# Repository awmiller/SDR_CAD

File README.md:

# sdr_eagle
various designs for different stages of development and manufacturers.

## 1: Clone into the "eagle" directory created by the Eagle CAD installer
## 2: Copy contents of "copy_to_lbr" into your "<Eagle Install dir>/lbr"

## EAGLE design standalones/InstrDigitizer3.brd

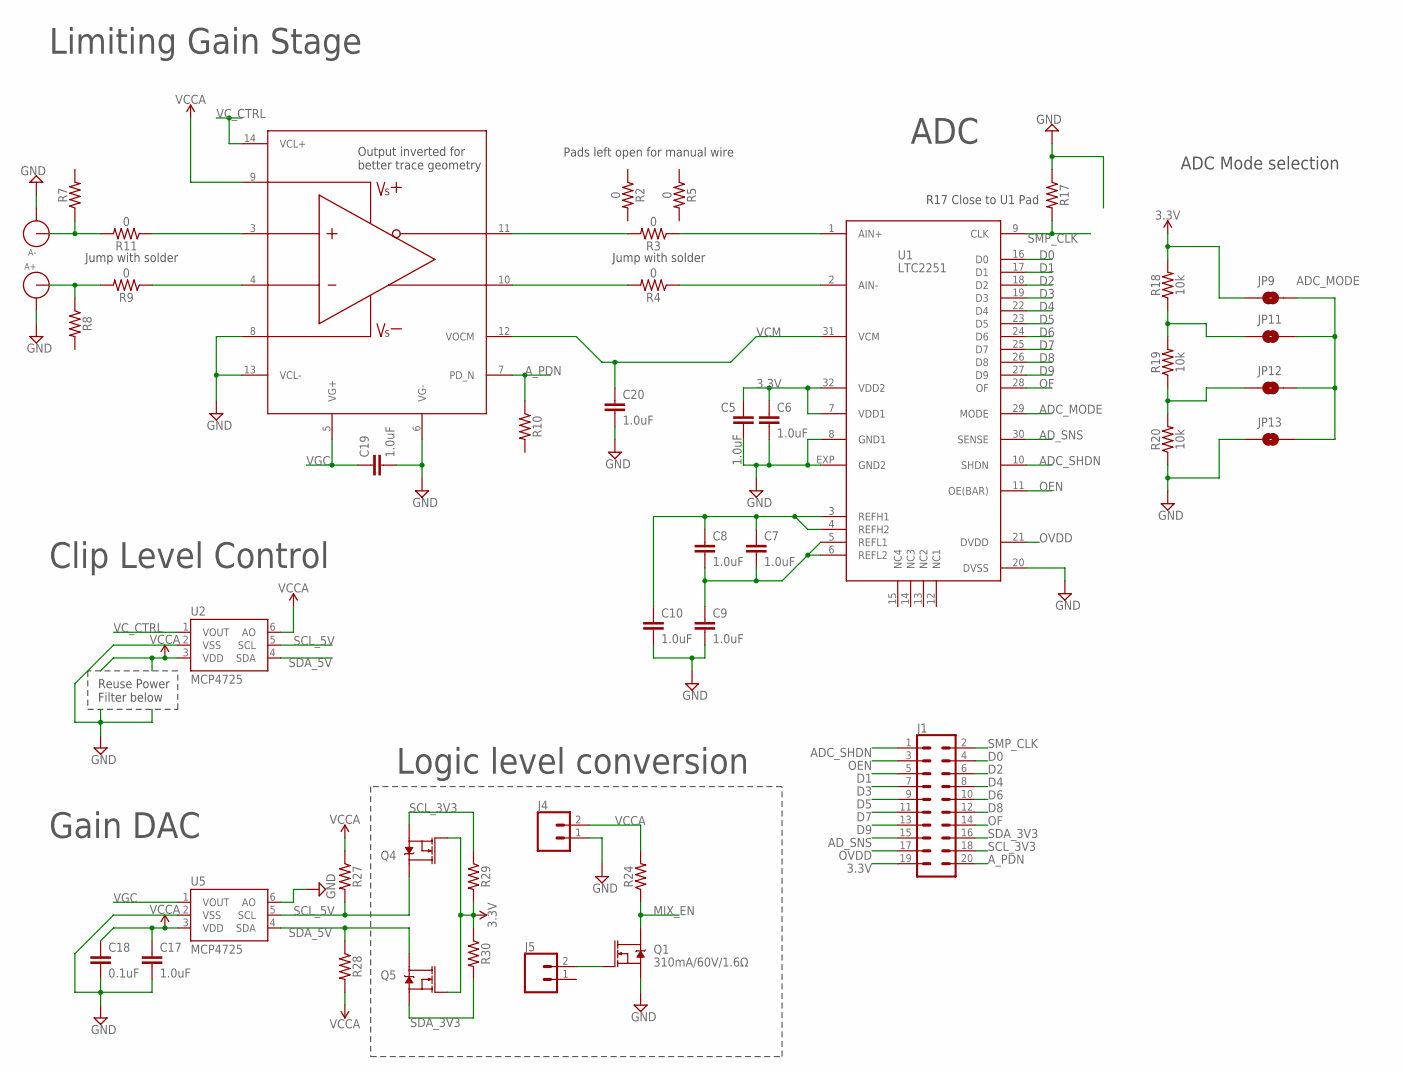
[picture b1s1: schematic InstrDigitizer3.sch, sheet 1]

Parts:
A+: LINX-SMA-EDGE-0.062; CONSMA003.062
A-: LINX-SMA-EDGE-0.062; CONSMA003.062
C5, C6, C7, C8, C9, C10, C17, C19, C20: 1.0uF; 0402
C18: 0.1uF; 0402
J1: CONN_10X2; 2X10
J4, J5: CONN_02; 1X02
JP9, JP11, JP12, JP13: JUMPER-SMT_2_NO_NO-SILK; SMT-JUMPER_2_NO_NO-SILK
Q1: 310mA/60V/1.6Ω; SOT323
Q4, Q5: MOSFET-NCH-AO3404A; SOT23-3
R2, R3, R4, R5, R9, R11: 0; 0402
R7, R8, R10, R17, R24, R27, R28, R29, R30: 0402
R18, R19, R20: 10k; 0402
U1: LTC2251; HVQFN32
U2, U5: MCP4725; SOT23-6
U$1: THS7530; TSSOP14

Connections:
3.3V: C5.1, C6.1, J1.19, JP9.1, Q4.1 (G), Q5.1 (G), R18.2, R29.2, R30.1, U1.7 (VDD1), U1.32 (VDD2); also elsewhere on the board
ADC_MODE: JP9.2, JP11.2, JP12.2, JP13.2, U1.29 (MODE)
ADC_SHDN: J1.1, U1.10 (SHDN)
AD_SNS: J1.15, U1.30 (SENSE)
A_PDN: J1.20, R10.1, U$1.7 (PD_N)
D0: J1.4, U1.16 (D0)
D1: J1.5, U1.17 (D1)
D2: J1.6, U1.18 (D2)
D3: J1.7, U1.19 (D3)
D4: J1.8, U1.22 (D4)
D5: J1.9, U1.23 (D5)
D6: J1.10, U1.24 (D6)
D7: J1.11, U1.25 (D7)
D8: J1.12, U1.26 (D8)
D9: J1.13, U1.27 (D9)
GND: A+.GND1, A+.GND2, A+.GND3, A+.GND4, A-.GND1, A-.GND2, A-.GND3, A-.GND4, C5.2, C6.2, C9.2, C10.2, C17.2, C18.2, C19.2, C20.2, J4.1, JP13.1, Q1.2 (S), R17.1, R20.1, U1.8 (GND1), U1.20 (DVSS), U1.EXP (GND2), U2.2 (VSS), U5.2 (VSS), U5.6 (AO), U$1.6 (VG-), U$1.8, U$1.13 (VCL-); also elsewhere on the board
MIX_EN: Q1.3 (D), R24.1; also elsewhere on the board
unnamed: R11.1, U$1.3
unnamed: A+.ANT, R8.1, R9.2
unnamed: J5.2, Q1.1 (G)
unnamed: R3.1, U1.1 (AIN+)
unnamed: R3.2, U$1.11 (VO-)
unnamed: R4.1, U1.2 (AIN-)
unnamed: R4.2, U$1.10 (VO+)
unnamed: A-.ANT, R7.1, R11.2
unnamed: R9.1, U$1.4
unnamed: C7.1, C8.1, C10.1, U1.3 (REFH1), U1.4 (REFH2)
unnamed: JP12.1, R19.1, R20.2
unnamed: C7.2, C8.2, C9.1, U1.5 (REFL1), U1.6 (REFL2)
unnamed: JP11.1, R18.1, R19.2
OEN: J1.3, U1.11 (OE(BAR))
OF: J1.14, U1.28 (OF)
OVDD: J1.17, U1.21 (DVDD)
SCL_3V3: J1.18, Q4.2 (S), R29.1
SCL_5V: Q4.3 (D), R27.2, U2.5 (SCL), U5.5 (SCL)
SDA_3V3: J1.16, Q5.2 (S), R30.2
SDA_5V: Q5.3 (D), R28.1, U2.4 (SDA), U5.4 (SDA)
SMP_CLK: J1.2, R17.2, U1.9 (CLK)
VCCA: C17.1, C18.1, J4.2, R24.2, R27.1, R28.2, U2.3 (VDD), U2.6 (AO), U5.3 (VDD), U$1.9; also elsewhere on the board
VCM: C20.1, U1.31 (VCM), U$1.12 (VOCM)
VC_CTRL: U2.1 (VOUT), U$1.14 (VCL+)
VGC: C19.1, U5.1 (VOUT), U$1.5 (VG+)

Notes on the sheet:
R17 Close to U1 Pad
Logic level conversion
Limiting Gain Stage
ADC
Gain DAC
ADC Mode selection
Jump with solder
Pads left open for manual wire
Clip Level Control
Output inverted for better trace geometry
Reuse Power Filter below

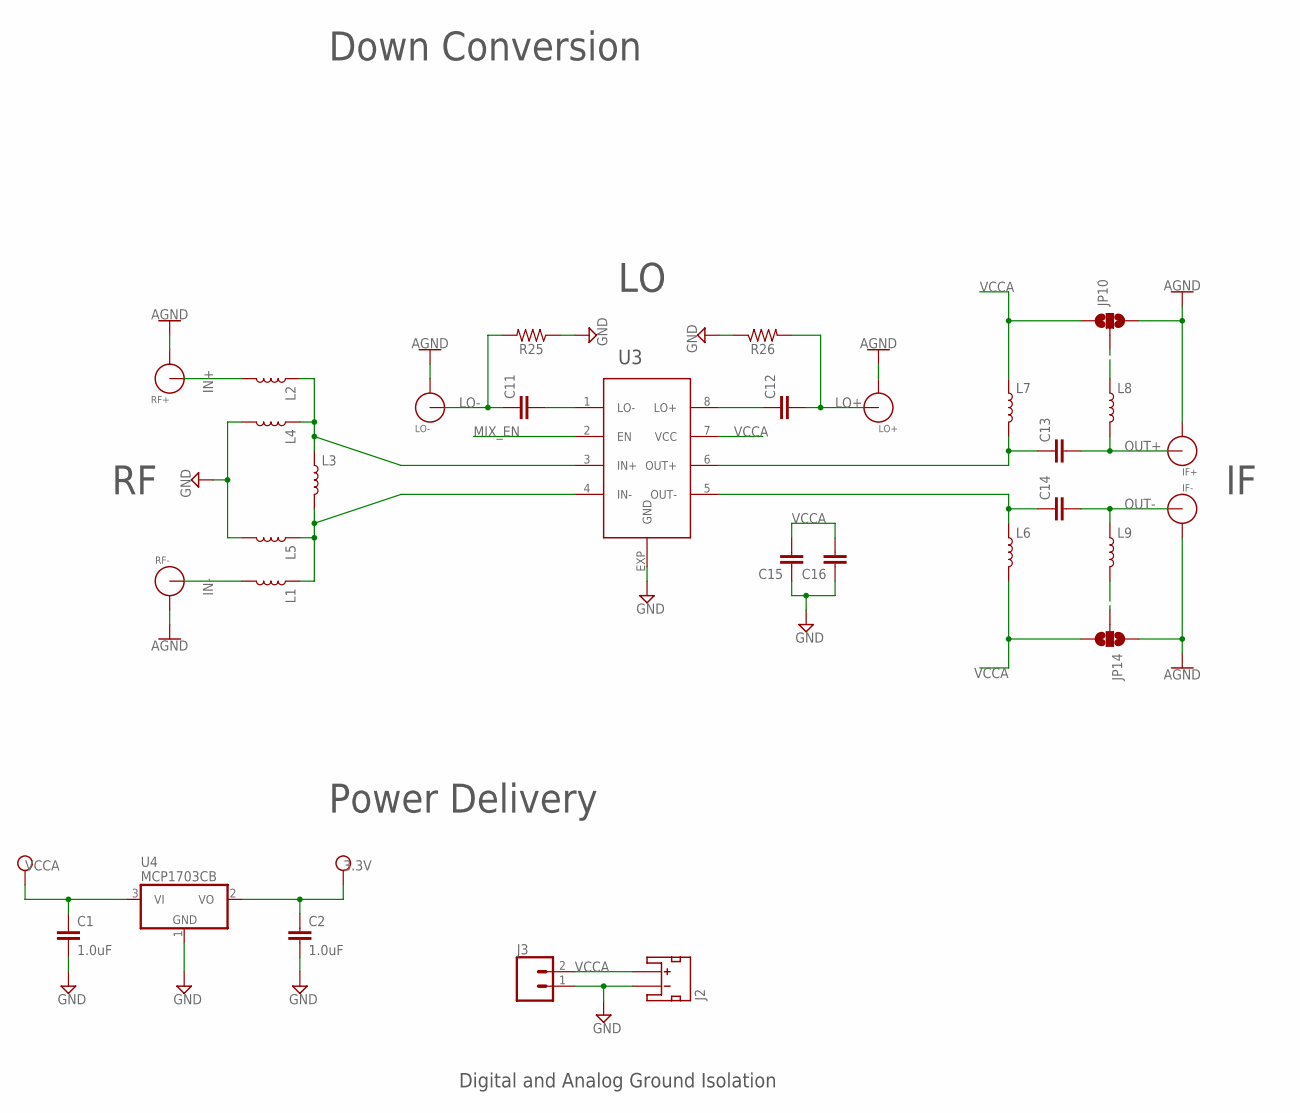
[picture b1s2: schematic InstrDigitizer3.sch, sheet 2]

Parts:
C1, C2: 1.0uF; 0402
C11, C12, C13, C14, C15, C16: 1.0UF-0402-16V-10%; 0402
IF+: LINX-SMA-EDGE-0.062; CONSMA003.062
IF-: LINX-SMA-EDGE-0.062; CONSMA003.062
J2: JST_2MM_MALE; JST-2-SMD
J3: CONN_02; 1X02
JP10, JP14: JUMPER-SMT_3_NO_NO-SILK; SMT-JUMPER_3_NO_NO-SILK
L1, L2, L3, L4, L5, L6, L7, L8, L9: INDUCTOR-0603-33NH; 0603
LO+: LINX-SMA-EDGE-0.062; CONSMA003.062
LO-: LINX-SMA-EDGE-0.062; CONSMA003.062
R25, R26: 0402
RF+: LINX-SMA-EDGE-0.062; CONSMA003.062
RF-: LINX-SMA-EDGE-0.062; CONSMA003.062
U3: LT5560; DFN8-3X3
U4: MCP1703CB; SOT23

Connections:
3.3V: C2.1, U4.2 (VO); also elsewhere on the board
GND: C1.2, C2.2, C15.1, C16.1, IF+.GND1, IF+.GND2, IF+.GND3, IF+.GND4, IF-.GND1, IF-.GND2, IF-.GND3, IF-.GND4, J2.1 (-), J3.1, JP10.3, JP14.1, L4.2, L5.2, LO+.GND1, LO+.GND2, LO+.GND3, LO+.GND4, LO-.GND1, LO-.GND2, LO-.GND3, LO-.GND4, R25.1, R26.1, RF+.GND1, RF+.GND2, RF+.GND3, RF+.GND4, RF-.GND1, RF-.GND2, RF-.GND3, RF-.GND4, U3.EXP (GND), U4.1 (GND); also elsewhere on the board
IN+: L2.2, RF+.ANT
IN-: L1.2, RF-.ANT
LO+: C12.2, LO+.ANT, R26.2
LO-: C11.1, LO-.ANT, R25.2
MIX_EN: U3.2 (EN); also elsewhere on the board
N98: L1.1, L3.2, L5.1, U3.4 (IN-)
unnamed: C11.2, U3.1 (LO-)
unnamed: C12.1, U3.8 (LO+)
unnamed: L2.1, L3.1, L4.1, U3.3 (IN+)
unnamed: C14.1, L6.1, U3.5 (OUT-)
unnamed: C13.1, L7.2, U3.6 (OUT+)
unnamed: JP10.2, L8.1
unnamed: JP14.2, L9.2
OUT+: C13.2, IF+.ANT, L8.2
OUT-: C14.2, IF-.ANT, L9.1
VCCA: C1.1, C15.2, C16.2, J2.2 (+), J3.2, JP10.1, JP14.3, L6.2, L7.1, U3.7 (VCC), U4.3 (VI); also elsewhere on the board

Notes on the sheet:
Digital and Analog Ground Isolation
Power Delivery
Down Conversion

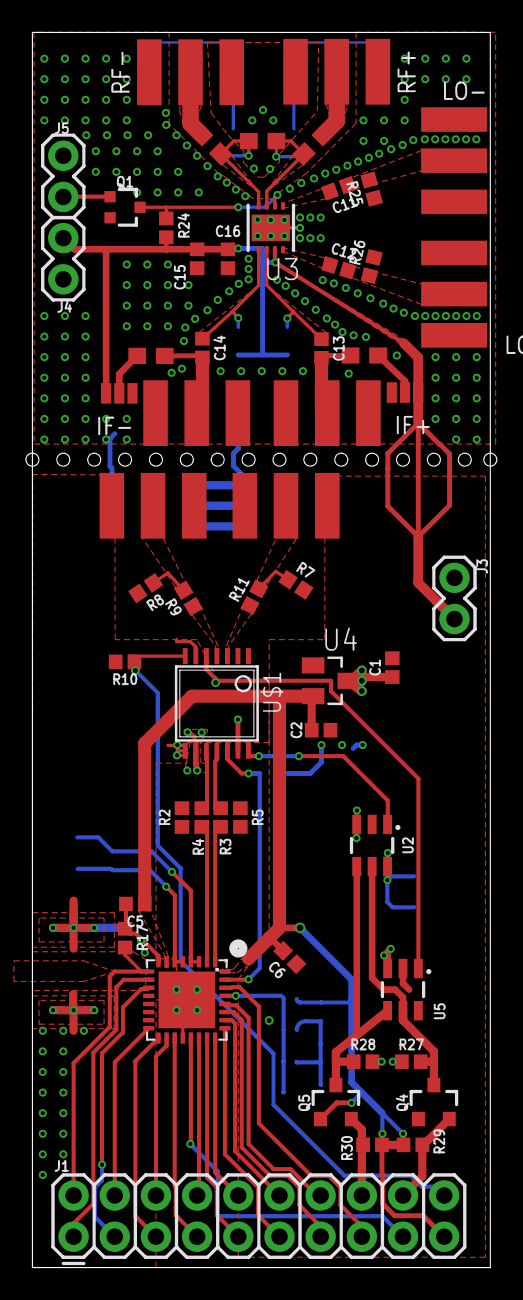
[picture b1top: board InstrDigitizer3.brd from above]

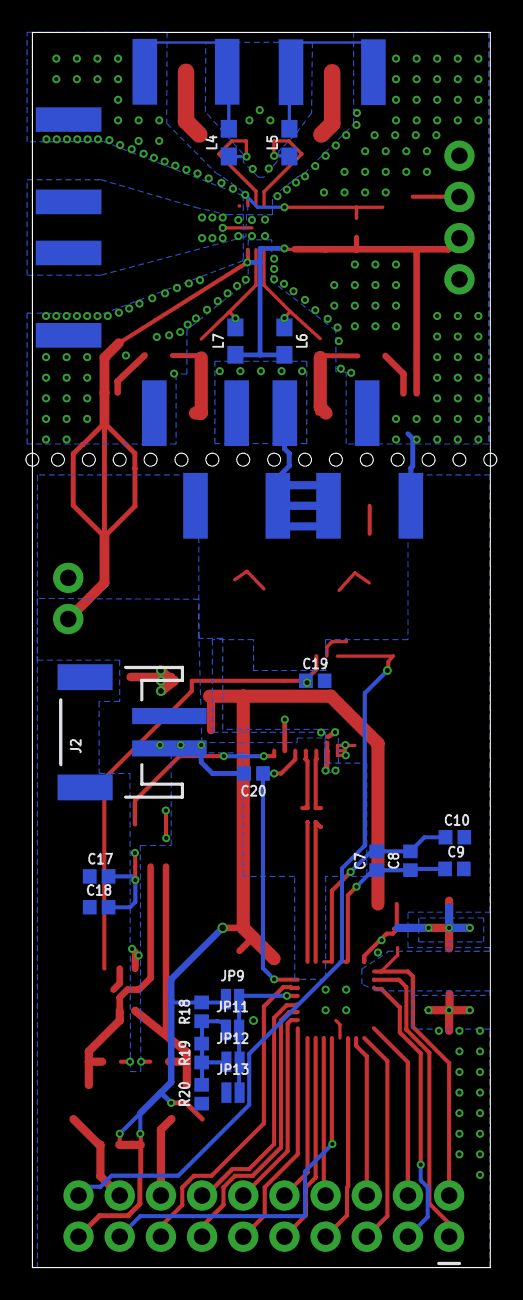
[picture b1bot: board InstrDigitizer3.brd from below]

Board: 2 copper layers, 28.2 x 76.2 mm, 75 parts (20 on the bottom side), 56 nets.

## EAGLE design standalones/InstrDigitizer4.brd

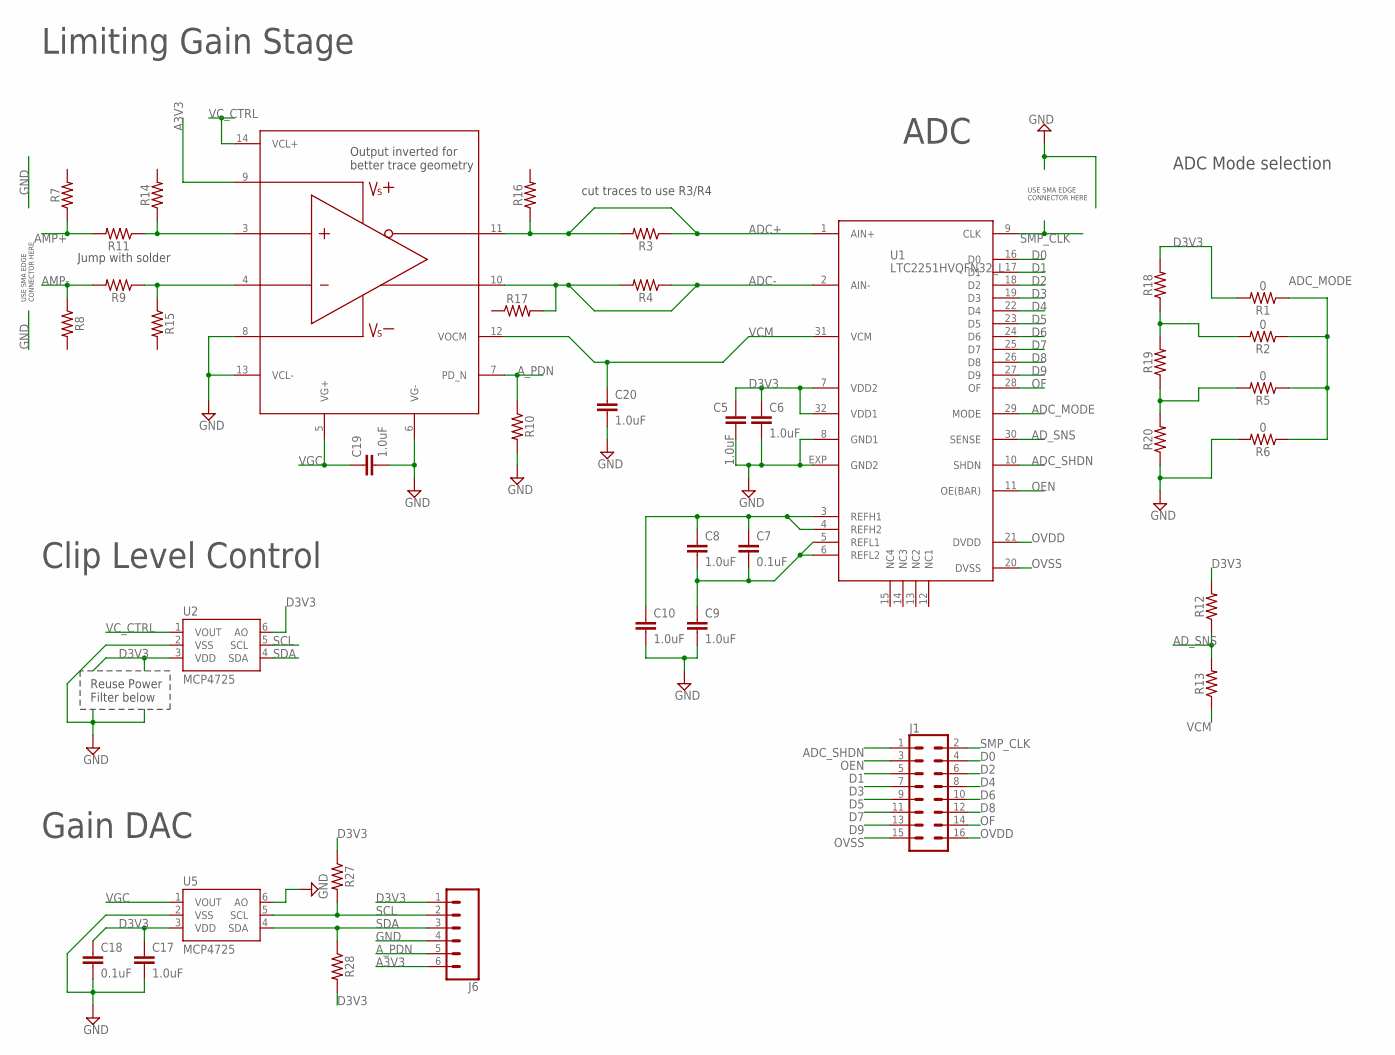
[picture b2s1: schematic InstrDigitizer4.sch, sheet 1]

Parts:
C5, C6, C8, C9, C10, C17, C19, C20: 1.0uF; 0402
C7, C18: 0.1uF; 0402
J1: CONN_08X2; 2X8
J6: CONN_06SILK_FEMALE_PTH; 1X06
R1, R2, R5, R6: 0; 0402
R3, R4, R7, R8, R9, R10, R11, R12, R13, R14, R15, R16, R17, R18, R19, R20, R27, R28: 0402
U1: LTC2251HVQFN32_L; HVQFN32_LONG
U2, U5: MCP4725; SOT23-6
U$1: THS7530TSSOP14_LONG; TSSOP14_LONG

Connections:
A3V3: J6.6, U$1.9; also elsewhere on the board
ADC+: R3.1, R3.2, R16.1, U1.1 (AIN+), U$1.11 (VO-)
ADC-: R4.1, R4.2, R17.2, U1.2 (AIN-), U$1.10 (VO+)
ADC_MODE: R1.1, R2.1, R5.1, R6.1, U1.29 (MODE)
ADC_SHDN: J1.1, U1.10 (SHDN)
AD_SNS: R12.1, R13.2, U1.30 (SENSE)
AMP+: R7.1, R11.2
AMP-: R8.1, R9.2
A_PDN: J6.5, R10.1, U$1.7 (PD_N)
D0: J1.4, U1.16 (D0)
D1: J1.5, U1.17 (D1)
D2: J1.6, U1.18 (D2)
D3: J1.7, U1.19 (D3)
D3V3: C5.1, C6.1, C17.1, C18.1, J6.1, R1.2, R12.2, R18.2, R27.1, R28.2, U1.7 (VDD2), U1.32 (VDD1), U2.3 (VDD), U2.6 (AO), U5.3 (VDD); also elsewhere on the board
D4: J1.8, U1.22 (D4)
D5: J1.9, U1.23 (D5)
D6: J1.10, U1.24 (D6)
D7: J1.11, U1.25 (D7)
D8: J1.12, U1.26 (D8)
D9: J1.13, U1.27 (D9)
GND: C5.2, C6.2, C9.2, C10.2, C17.2, C18.2, C19.2, C20.2, J6.4, R6.2, R10.2, R20.1, U1.8 (GND1), U1.EXP (GND2), U2.2 (VSS), U5.2 (VSS), U5.6 (AO), U$1.6 (VG-), U$1.8, U$1.13 (VCL-); also elsewhere on the board
unnamed: R11.1, R14.1, U$1.3
unnamed: R9.1, R15.1, U$1.4
unnamed: C7.1, C8.1, C10.1, U1.3 (REFH1), U1.4 (REFH2)
unnamed: R5.2, R19.1, R20.2
unnamed: C7.2, C8.2, C9.1, U1.5 (REFL1), U1.6 (REFL2)
unnamed: R2.2, R18.1, R19.2
OEN: J1.3, U1.11 (OE(BAR))
OF: J1.14, U1.28 (OF)
OVDD: J1.16, U1.21 (DVDD)
OVSS: J1.15, U1.20 (DVSS)
SCL: J6.2, R27.2, U2.5 (SCL), U5.5 (SCL)
SDA: J6.3, R28.1, U2.4 (SDA), U5.4 (SDA)
SMP_CLK: J1.2, U1.9 (CLK)
VCM: C20.1, R13.1, U1.31 (VCM), U$1.12 (VOCM)
VC_CTRL: U2.1 (VOUT), U$1.14 (VCL+)
VGC: C19.1, U5.1 (VOUT), U$1.5 (VG+)

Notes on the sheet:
Limiting Gain Stage
ADC
Gain DAC
ADC Mode selection
Clip Level Control
Output inverted for better trace geometry
Reuse Power Filter below
Jump with solder
USE SMA EDGE CONNECTOR HERE
cut traces to use R3/R4

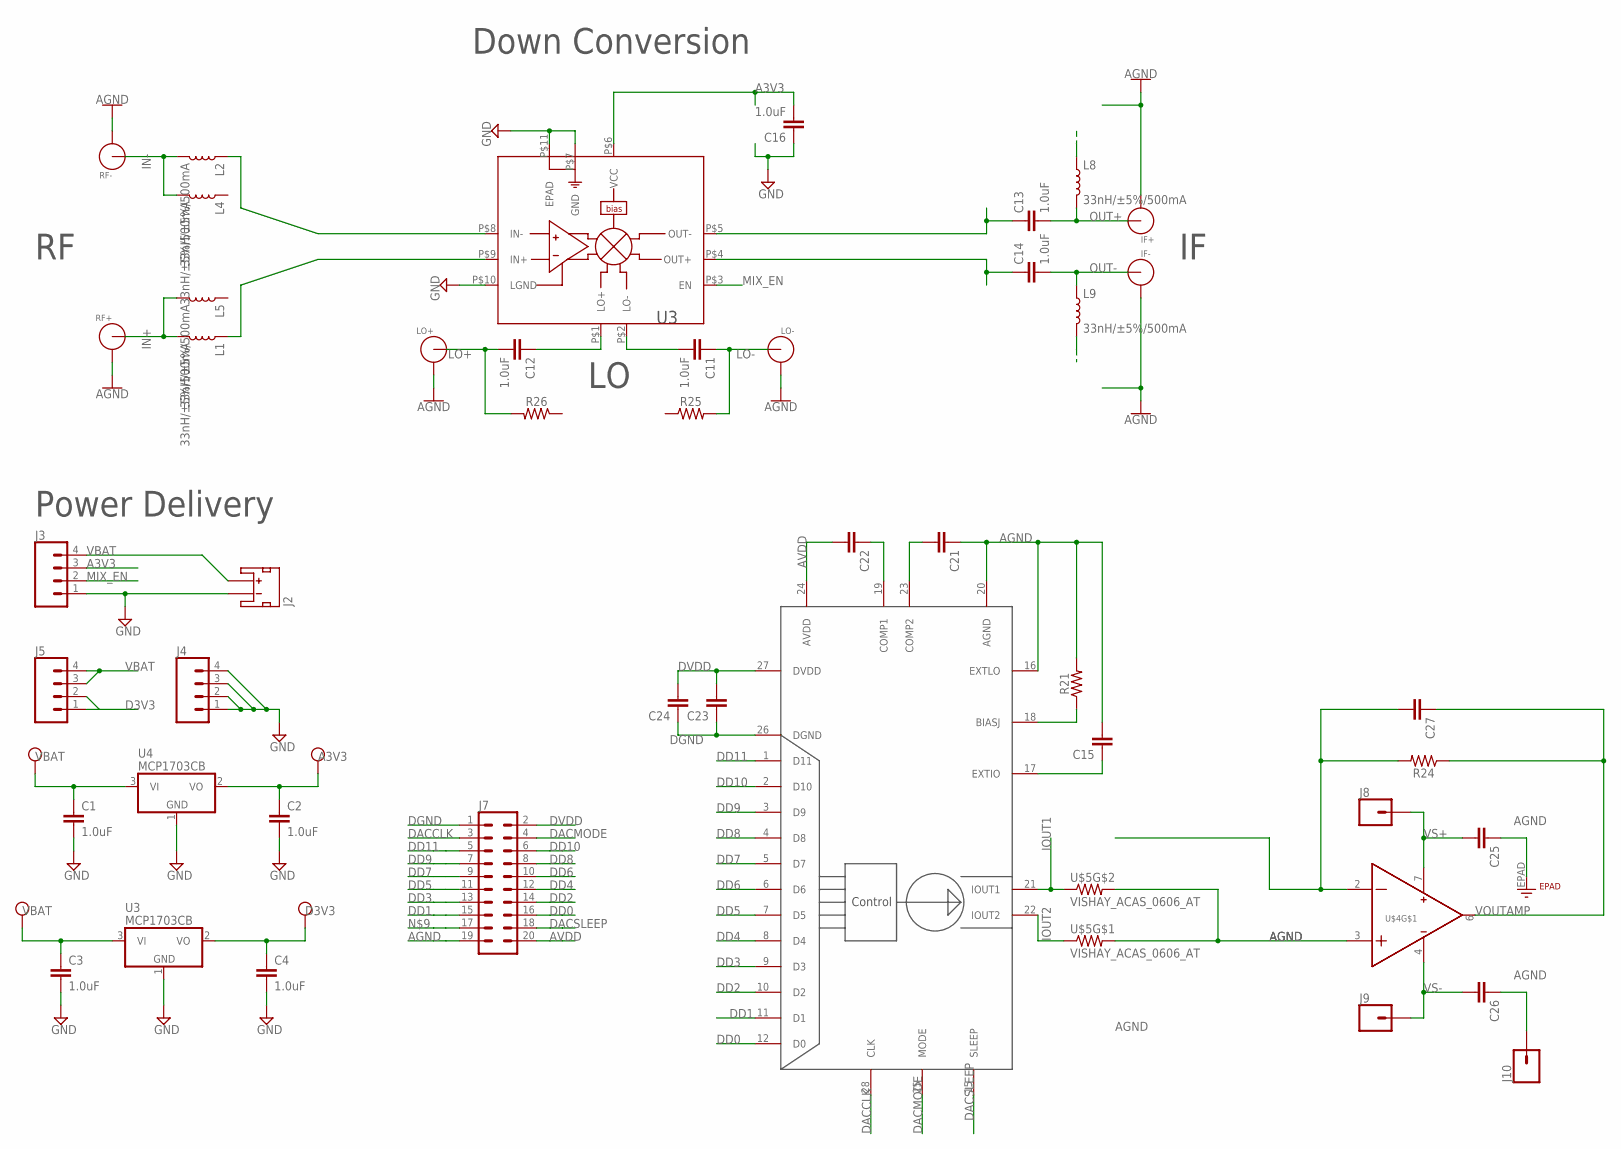
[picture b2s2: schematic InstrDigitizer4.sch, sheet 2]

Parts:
C1, C2, C3, C4, C11, C12, C13, C14, C16: 1.0uF; 0402
C15, C21, C22, C23, C24, C25, C26, C27: 1.0UF-0402-16V-10%; 0402
IF+: LINX-SMA-EDGE-0.062; CONSMA003.062
IF-: LINX-SMA-EDGE-0.062; CONSMA003.062
J2: JST_2MM_MALE; JST-2-SMD
J3, J4, J5: CONN_04; 1X04
J7: CONN_10X2; 2X10
J8, J9, J10: CONN_01; 1X01
L1, L2, L4, L5, L8, L9: 33nH/±5%/500mA; 0603
LO+: LINX-SMA-EDGE-0.062; CONSMA003.062
LO-: LINX-SMA-EDGE-0.062; CONSMA003.062
R21, R24, R25, R26: 0402
RF+: LINX-SMA-EDGE-0.062; CONSMA003.062
RF-: LINX-SMA-EDGE-0.062; CONSMA003.062
U3, U4: MCP1703CB; SOT23
U$2: THS5661ASOIC28; SOIC-28
U$3: LTC5562LONG; QFN_10_2X2MM_05-08-1534_LONG
U$4: THS4011SOIC8-EPAD; SO-08
U$5: VISHAY_ACAS_0606_AT; VISHAY_ACAS0606AT

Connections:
A3V3: C2.1, C16.2, J3.3, U4.2 (VO), U$3.P$6 (VCC); also elsewhere on the board
AGND: C15.2, C21.1, C25.1, C26.1, J7.19, J10.1, R21.2, U$2.16 (EXTLO), U$2.20 (AGND), U$4.3 (IN+), U$4.EPAD, U$5.P$3 (2), U$5.P$4 (2)
AVDD: C22.2, J7.20, U$2.24 (AVDD)
D3V3: C4.1, J5.1, J5.2, U3.2 (VO); also elsewhere on the board
DACCLK: J7.3, U$2.28 (CLK)
DACMODE: J7.4, U$2.25 (MODE)
DACSLEEP: J7.18, U$2.15 (SLEEP)
DD0: J7.16, U$2.12 (D0)
DD1: J7.15, U$2.11 (D1)
DD2: J7.14, U$2.10 (D2)
DD3: J7.13, U$2.9 (D3)
DD4: J7.12, U$2.8 (D4)
DD5: J7.11, U$2.7 (D5)
DD6: J7.10, U$2.6 (D6)
DD7: J7.9, U$2.5 (D7)
DD8: J7.8, U$2.4 (D8)
DD9: J7.7, U$2.3 (D9)
DD10: J7.6, U$2.2 (D10)
DD11: J7.5, U$2.1 (D11)
DGND: C23.1, C24.1, J7.1, U$2.26 (DGND)
DVDD: C23.2, C24.2, J7.2, U$2.27 (DVDD)
GND: C1.2, C2.2, C3.2, C4.2, C16.1, IF+.GND1, IF+.GND2, IF+.GND3, IF+.GND4, IF-.GND1, IF-.GND2, IF-.GND3, IF-.GND4, J2.1 (-), J3.1, J4.1, J4.2, J4.3, J4.4, LO+.GND1, LO+.GND2, LO+.GND3, LO+.GND4, LO-.GND1, LO-.GND2, LO-.GND3, LO-.GND4, RF+.GND1, RF+.GND2, RF+.GND3, RF+.GND4, RF-.GND1, RF-.GND2, RF-.GND3, RF-.GND4, U3.1 (GND), U4.1 (GND), U$3.P$7 (GND), U$3.P$10 (LGND), U$3.P$11 (EPAD); also elsewhere on the board
IN+: L1.2, L5.2, RF+.ANT
IN-: L2.2, L4.2, RF-.ANT
IOUT1: U$2.21 (IOUT1), U$5.P$2 (1)
IOUT2: U$2.22 (IOUT2), U$5.P$1 (1)
LO+: C12.2, LO+.ANT, R26.2
LO-: C11.1, LO-.ANT, R25.2
MIX_EN: J3.2, U$3.P$3 (EN)
N98: L1.1, U$3.P$9 (IN+)
unnamed: C15.1, U$2.17 (EXTIO)
unnamed: R21.1, U$2.18 (BIASJ)
unnamed: C21.2, U$2.23 (COMP2)
unnamed: C22.1, U$2.19 (COMP1)
unnamed: C27.2, R24.2, U$4.2 (IN-)
unnamed: C11.2, U$3.P$2 (LO-)
unnamed: C12.1, U$3.P$1 (LO+)
unnamed: L2.1, U$3.P$8 (IN-)
unnamed: C14.1, U$3.P$4 (OUT+)
unnamed: C13.1, U$3.P$5 (OUT-)
OUT+: C13.2, IF+.ANT, L8.2
OUT-: C14.2, IF-.ANT, L9.1
VBAT: C1.1, C3.1, J2.2 (+), J3.4, J5.3, J5.4, U3.3 (VI), U4.3 (VI)
VOUTAMP: C27.1, R24.1, U$4.6 (OUT)
VS+: C25.2, J8.1, U$4.7 (VCC+)
VS-: C26.2, J9.1, U$4.4 (VCC-)

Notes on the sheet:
Power Delivery
Down Conversion

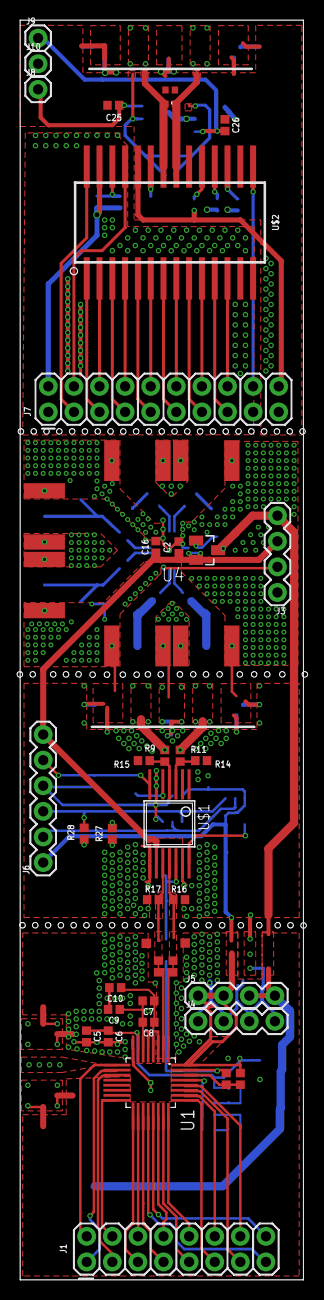
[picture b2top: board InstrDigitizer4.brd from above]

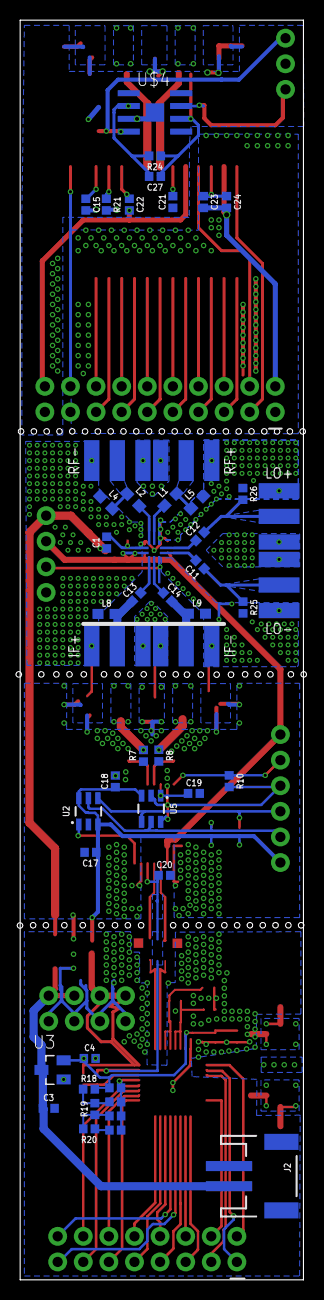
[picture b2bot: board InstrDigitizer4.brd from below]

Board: 2 copper layers, 28.1 x 125.0 mm, 85 parts (49 on the bottom side), 80 nets.

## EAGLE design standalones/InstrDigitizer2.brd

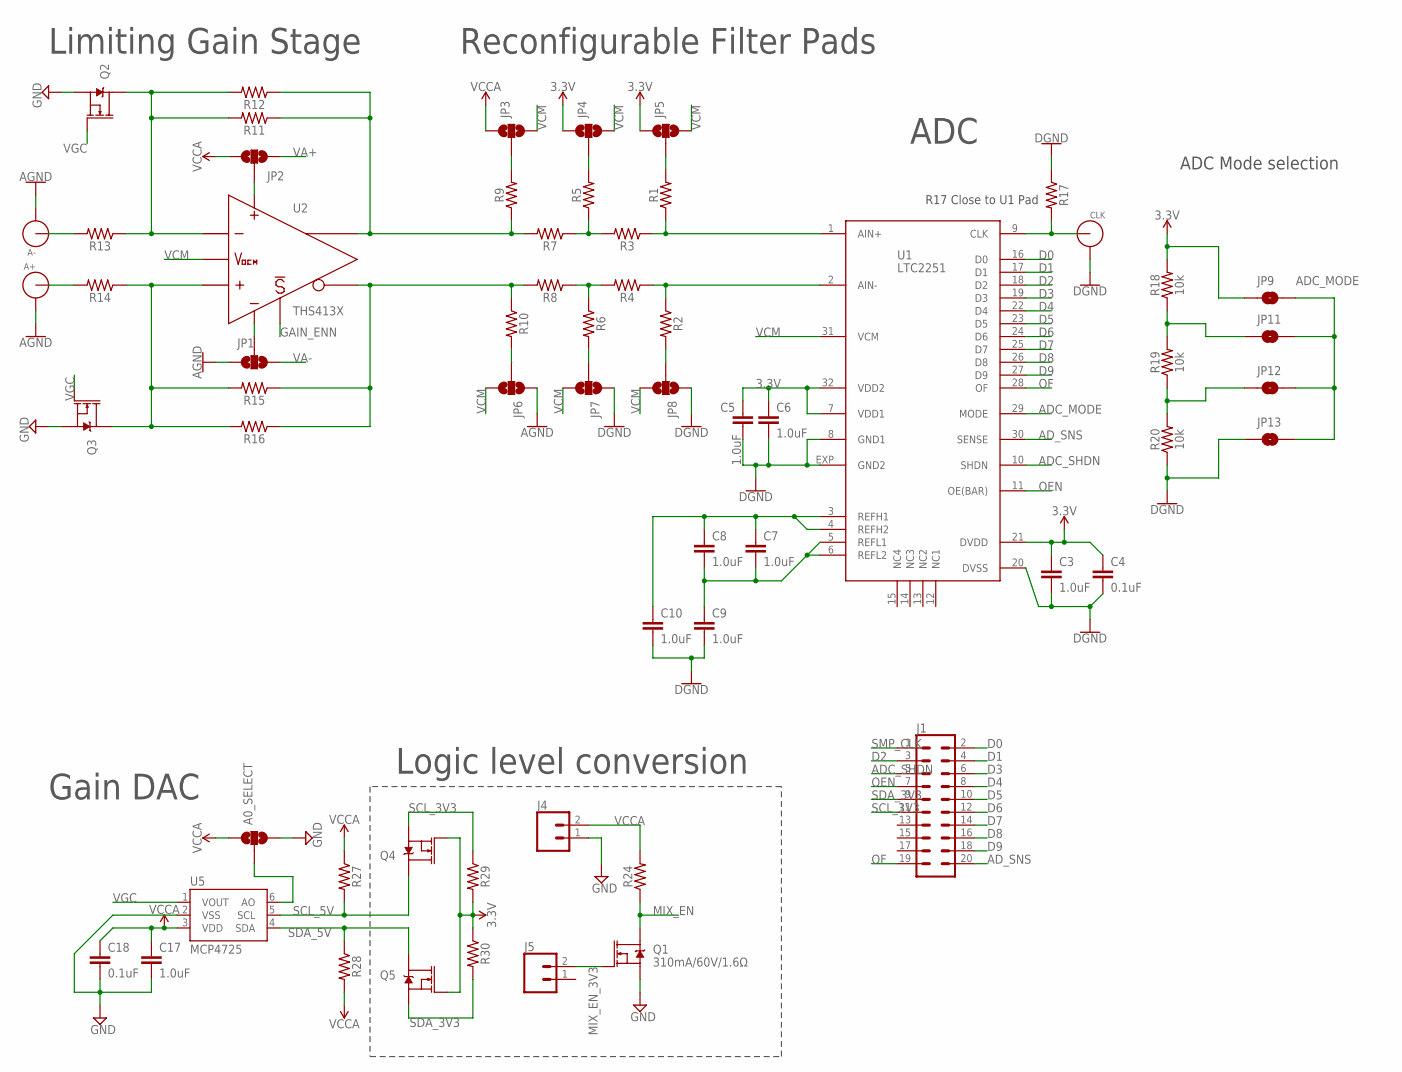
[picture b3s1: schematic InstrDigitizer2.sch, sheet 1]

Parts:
A0_SELECT: JUMPER-SMT_3_NO_SILK; SMT-JUMPER_3_NO_SILK
A+: LINX-SMA-EDGE-0.062; CONSMA003.062
A-: LINX-SMA-EDGE-0.062; CONSMA003.062
C3, C5, C6, C7, C8, C9, C10, C17: 1.0uF; 0402
C4, C18: 0.1uF; 0402
CLK: LINX-SMA-EDGE-0.062; CONSMA003.062
J1: CONN_10X2; 2X10
J4, J5: CONN_02; 1X02
JP1, JP2, JP3, JP4, JP5, JP6, JP7, JP8: JUMPER-SMT_3_NO_SILK; SMT-JUMPER_3_NO_SILK
JP9, JP11, JP12, JP13: JUMPER-SMT_2_NO_NO-SILK; SMT-JUMPER_2_NO_NO-SILK
Q1: 310mA/60V/1.6Ω; SOT323
Q2, Q3, Q4, Q5: MOSFET-NCH-AO3404A; SOT23-3
R1, R2, R3, R4, R5, R6, R7, R8, R9, R10, R11, R12, R13, R14, R15, R16, R17, R24, R27, R28, R29, R30: 0402
R18, R19, R20: 10k; 0402
U1: LTC2251; HVQFN32
U2: THS413X; SO08
U5: MCP4725; SOT23-6

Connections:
3.3V: C3.1, C4.1, C5.1, C6.1, JP4.1, JP5.1, JP9.1, Q4.1 (G), Q5.1 (G), R18.2, R29.2, R30.1, U1.7 (VDD1), U1.21 (DVDD), U1.32 (VDD2); also elsewhere on the board
ADC_MODE: JP9.2, JP11.2, JP12.2, JP13.2, U1.29 (MODE)
ADC_SHDN: J1.5, U1.10 (SHDN)
AD_SNS: J1.20, U1.30 (SENSE)
AMP+: Q3.3 (D), R14.1, R15.2, R16.2, U2.8
AMP-: Q2.3 (D), R11.2, R12.2, R13.1, U2.1
D0: J1.2, U1.16 (D0)
D1: J1.4, U1.17 (D1)
D2: J1.3, U1.18 (D2)
D3: J1.6, U1.19 (D3)
D4: J1.8, U1.22 (D4)
D5: J1.10, U1.23 (D5)
D6: J1.12, U1.24 (D6)
D7: J1.14, U1.25 (D7)
D8: J1.16, U1.26 (D8)
D9: J1.18, U1.27 (D9)
GAIN_ENN: U2.7
GND: A0_SELECT.3, A+.GND1, A+.GND2, A+.GND3, A+.GND4, A-.GND1, A-.GND2, A-.GND3, A-.GND4, C3.2, C4.2, C5.2, C6.2, C9.2, C10.2, C17.2, C18.2, CLK.GND1, CLK.GND2, CLK.GND3, CLK.GND4, J4.1, JP1.3, JP6.1, JP7.1, JP8.1, JP13.1, Q1.2 (S), Q2.2 (S), Q3.2 (S), R17.1, R20.1, U1.8 (GND1), U1.20 (DVSS), U1.EXP (GND2), U5.2 (VSS); also elsewhere on the board
MIX_EN: Q1.3 (D), R24.1; also elsewhere on the board
MIX_EN_3V3: J5.2, Q1.1 (G)
unnamed: JP2.2, U2.3
unnamed: JP1.2, U2.6
unnamed: R7.2, R9.1, R11.1, R12.1, U2.4
unnamed: R3.2, R5.1, R7.1
unnamed: R1.1, R3.1, U1.1 (AIN+)
unnamed: R8.2, R10.1, R15.1, R16.1, U2.5
unnamed: R4.2, R6.1, R8.1
unnamed: R2.1, R4.1, U1.2 (AIN-)
unnamed: JP3.2, R9.2
unnamed: JP4.2, R5.2
unnamed: JP5.2, R1.2
unnamed: JP8.2, R2.2
unnamed: JP7.2, R6.2
unnamed: JP6.2, R10.2
unnamed: A-.ANT, R13.2
unnamed: A+.ANT, R14.2
unnamed: C7.1, C8.1, C10.1, U1.3 (REFH1), U1.4 (REFH2)
unnamed: JP12.1, R19.1, R20.2
unnamed: C7.2, C8.2, C9.1, U1.5 (REFL1), U1.6 (REFL2)
unnamed: JP11.1, R18.1, R19.2
unnamed: A0_SELECT.2, U5.6 (AO)
OEN: J1.7, U1.11 (OE(BAR))
OF: J1.19, U1.28 (OF)
SCL_3V3: J1.11, Q4.2 (S), R29.1
SCL_5V: Q4.3 (D), R27.2, U5.5 (SCL)
SDA_3V3: J1.9, Q5.2 (S), R30.2
SDA_5V: Q5.3 (D), R28.1, U5.4 (SDA)
SMP_CLK: CLK.ANT, J1.1, R17.2, U1.9 (CLK)
VA+: JP2.3
VA-: JP1.1
VCCA: A0_SELECT.1, C17.1, C18.1, J4.2, JP2.1, JP3.1, R24.2, R27.1, R28.2, U5.3 (VDD); also elsewhere on the board
VCM: JP3.3, JP4.3, JP5.3, JP6.3, JP7.3, JP8.3, U1.31 (VCM), U2.2
VGC: Q2.1 (G), Q3.1 (G), U5.1 (VOUT)

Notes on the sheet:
R17 Close to U1 Pad
Logic level conversion
Limiting Gain Stage
Reconfigurable Filter Pads
ADC
Gain DAC
ADC Mode selection

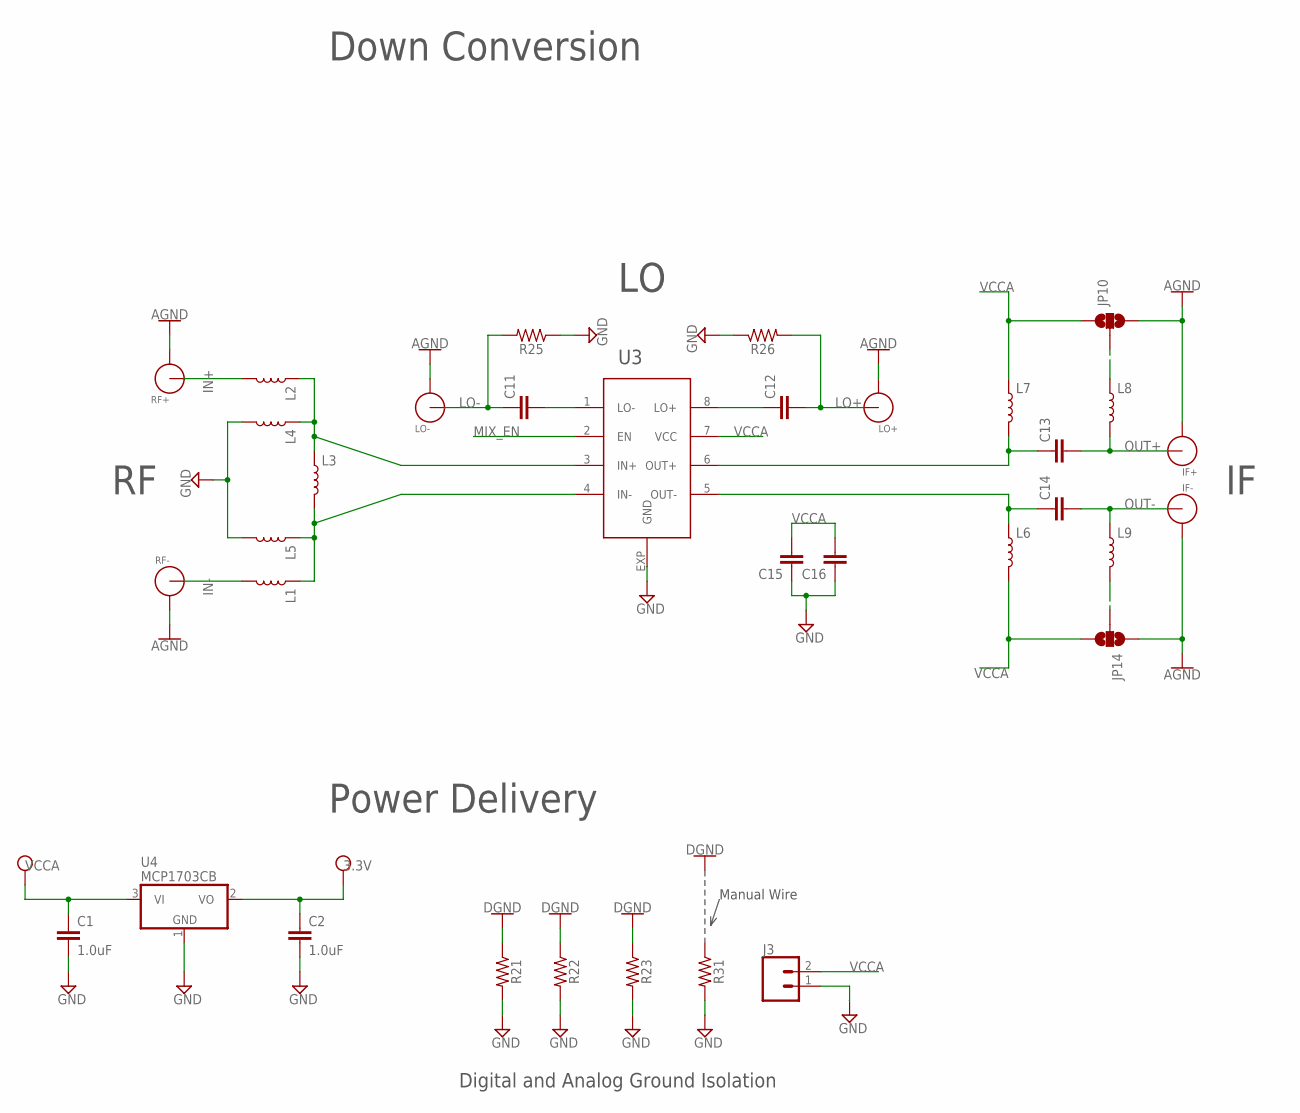
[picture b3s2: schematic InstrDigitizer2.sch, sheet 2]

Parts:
C1, C2: 1.0uF; 0402
C11, C12, C13, C14, C15, C16: 1.0UF-0402-16V-10%; 0402
IF+: LINX-SMA-EDGE-0.062; CONSMA003.062
IF-: LINX-SMA-EDGE-0.062; CONSMA003.062
J3: CONN_02; 1X02
JP10, JP14: JUMPER-SMT_3_NO_NO-SILK; SMT-JUMPER_3_NO_NO-SILK
L1, L2, L3, L4, L5, L6, L7, L8, L9: INDUCTOR-0603-33NH; 0603
LO+: LINX-SMA-EDGE-0.062; CONSMA003.062
LO-: LINX-SMA-EDGE-0.062; CONSMA003.062
R21, R22, R23, R25, R26, R31: 0402
RF+: LINX-SMA-EDGE-0.062; CONSMA003.062
RF-: LINX-SMA-EDGE-0.062; CONSMA003.062
U3: LT5560; DFN8-3X3
U4: MCP1703CB; SOT23

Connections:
3.3V: C2.1, U4.2 (VO); also elsewhere on the board
GND: C1.2, C2.2, C15.1, C16.1, IF+.GND1, IF+.GND2, IF+.GND3, IF+.GND4, IF-.GND1, IF-.GND2, IF-.GND3, IF-.GND4, J3.1, JP10.3, JP14.1, L4.2, L5.2, LO+.GND1, LO+.GND2, LO+.GND3, LO+.GND4, LO-.GND1, LO-.GND2, LO-.GND3, LO-.GND4, R21.1, R21.2, R22.1, R22.2, R23.1, R23.2, R25.1, R26.1, R31.2, RF+.GND1, RF+.GND2, RF+.GND3, RF+.GND4, RF-.GND1, RF-.GND2, RF-.GND3, RF-.GND4, U3.EXP (GND), U4.1 (GND); also elsewhere on the board
IN+: L2.2, RF+.ANT
IN-: L1.2, RF-.ANT
LO+: C12.2, LO+.ANT, R26.2
LO-: C11.1, LO-.ANT, R25.2
MIX_EN: U3.2 (EN); also elsewhere on the board
N98: L1.1, L3.2, L5.1, U3.4 (IN-)
unnamed: C11.2, U3.1 (LO-)
unnamed: C12.1, U3.8 (LO+)
unnamed: L2.1, L3.1, L4.1, U3.3 (IN+)
unnamed: C14.1, L6.1, U3.5 (OUT-)
unnamed: C13.1, L7.2, U3.6 (OUT+)
unnamed: JP10.2, L8.1
unnamed: JP14.2, L9.2
OUT+: C13.2, IF+.ANT, L8.2
OUT-: C14.2, IF-.ANT, L9.1
VCCA: C1.1, C15.2, C16.2, J3.2, JP10.1, JP14.3, L6.2, L7.1, U3.7 (VCC), U4.3 (VI); also elsewhere on the board

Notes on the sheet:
Digital and Analog Ground Isolation
Manual Wire
Power Delivery
Down Conversion

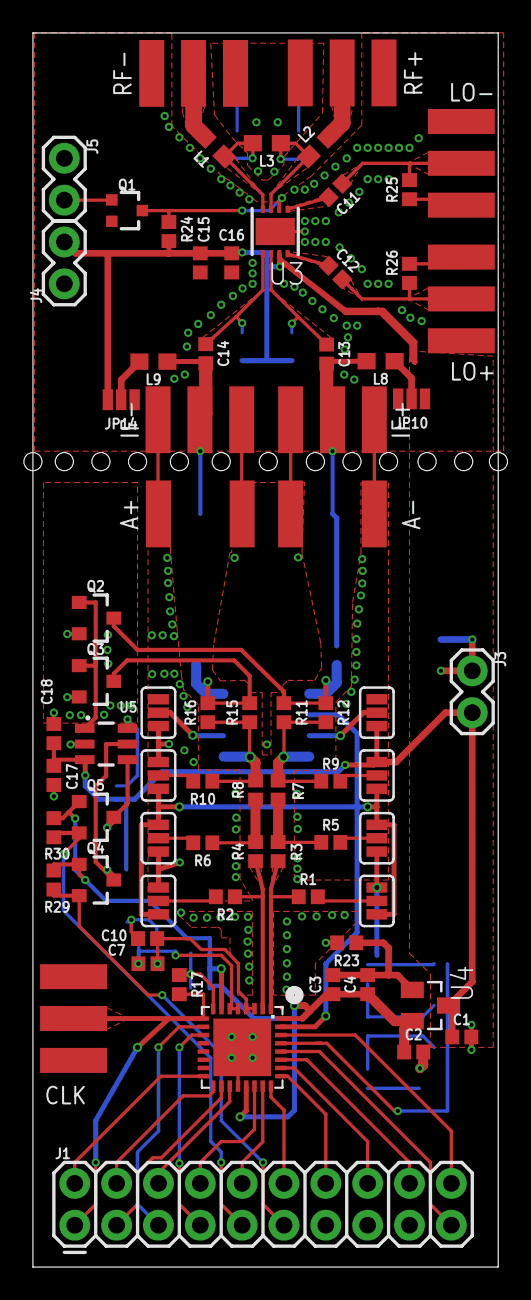
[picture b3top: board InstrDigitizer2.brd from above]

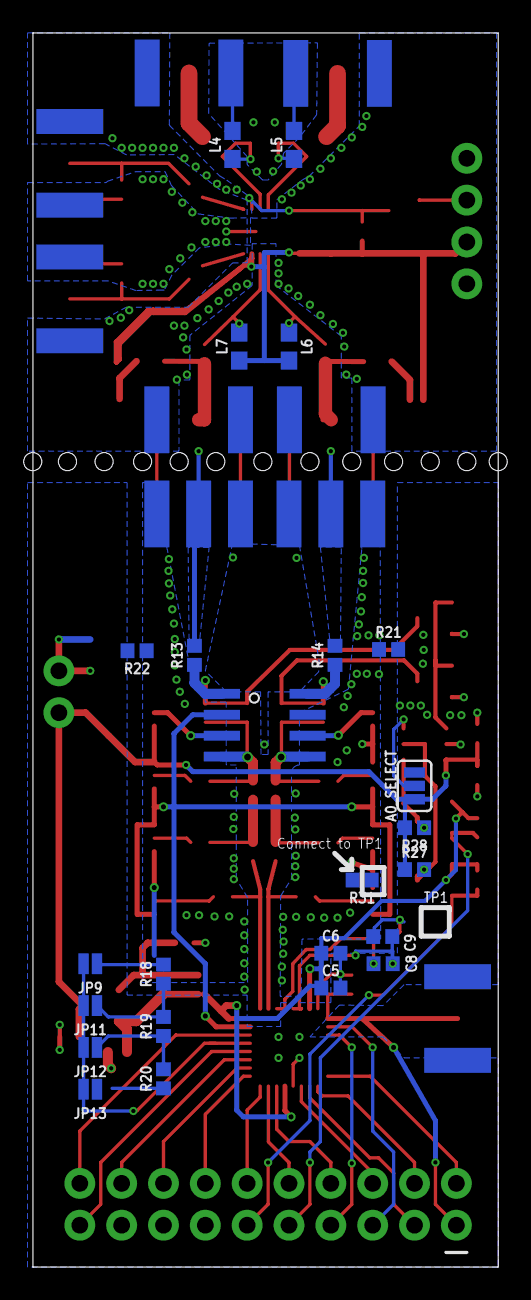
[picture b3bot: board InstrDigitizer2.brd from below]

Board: 2 copper layers, 28.2 x 74.9 mm, 96 parts (26 on the bottom side), 64 nets.

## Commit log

2018-01-22 initial add
    adding everything
2018-01-22 derpderpderp
2018-04-17 New board in Standalones, InstrDigitizer(4/5)
    added new parts with old ADC and capability to break away individual ICs.

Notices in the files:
parts and their libraries:
SparkFun-Jumpers: Licensing: Creative Commons ShareAlike 4.0 International - https://creativecommons.org/licenses/by-sa/4.0
